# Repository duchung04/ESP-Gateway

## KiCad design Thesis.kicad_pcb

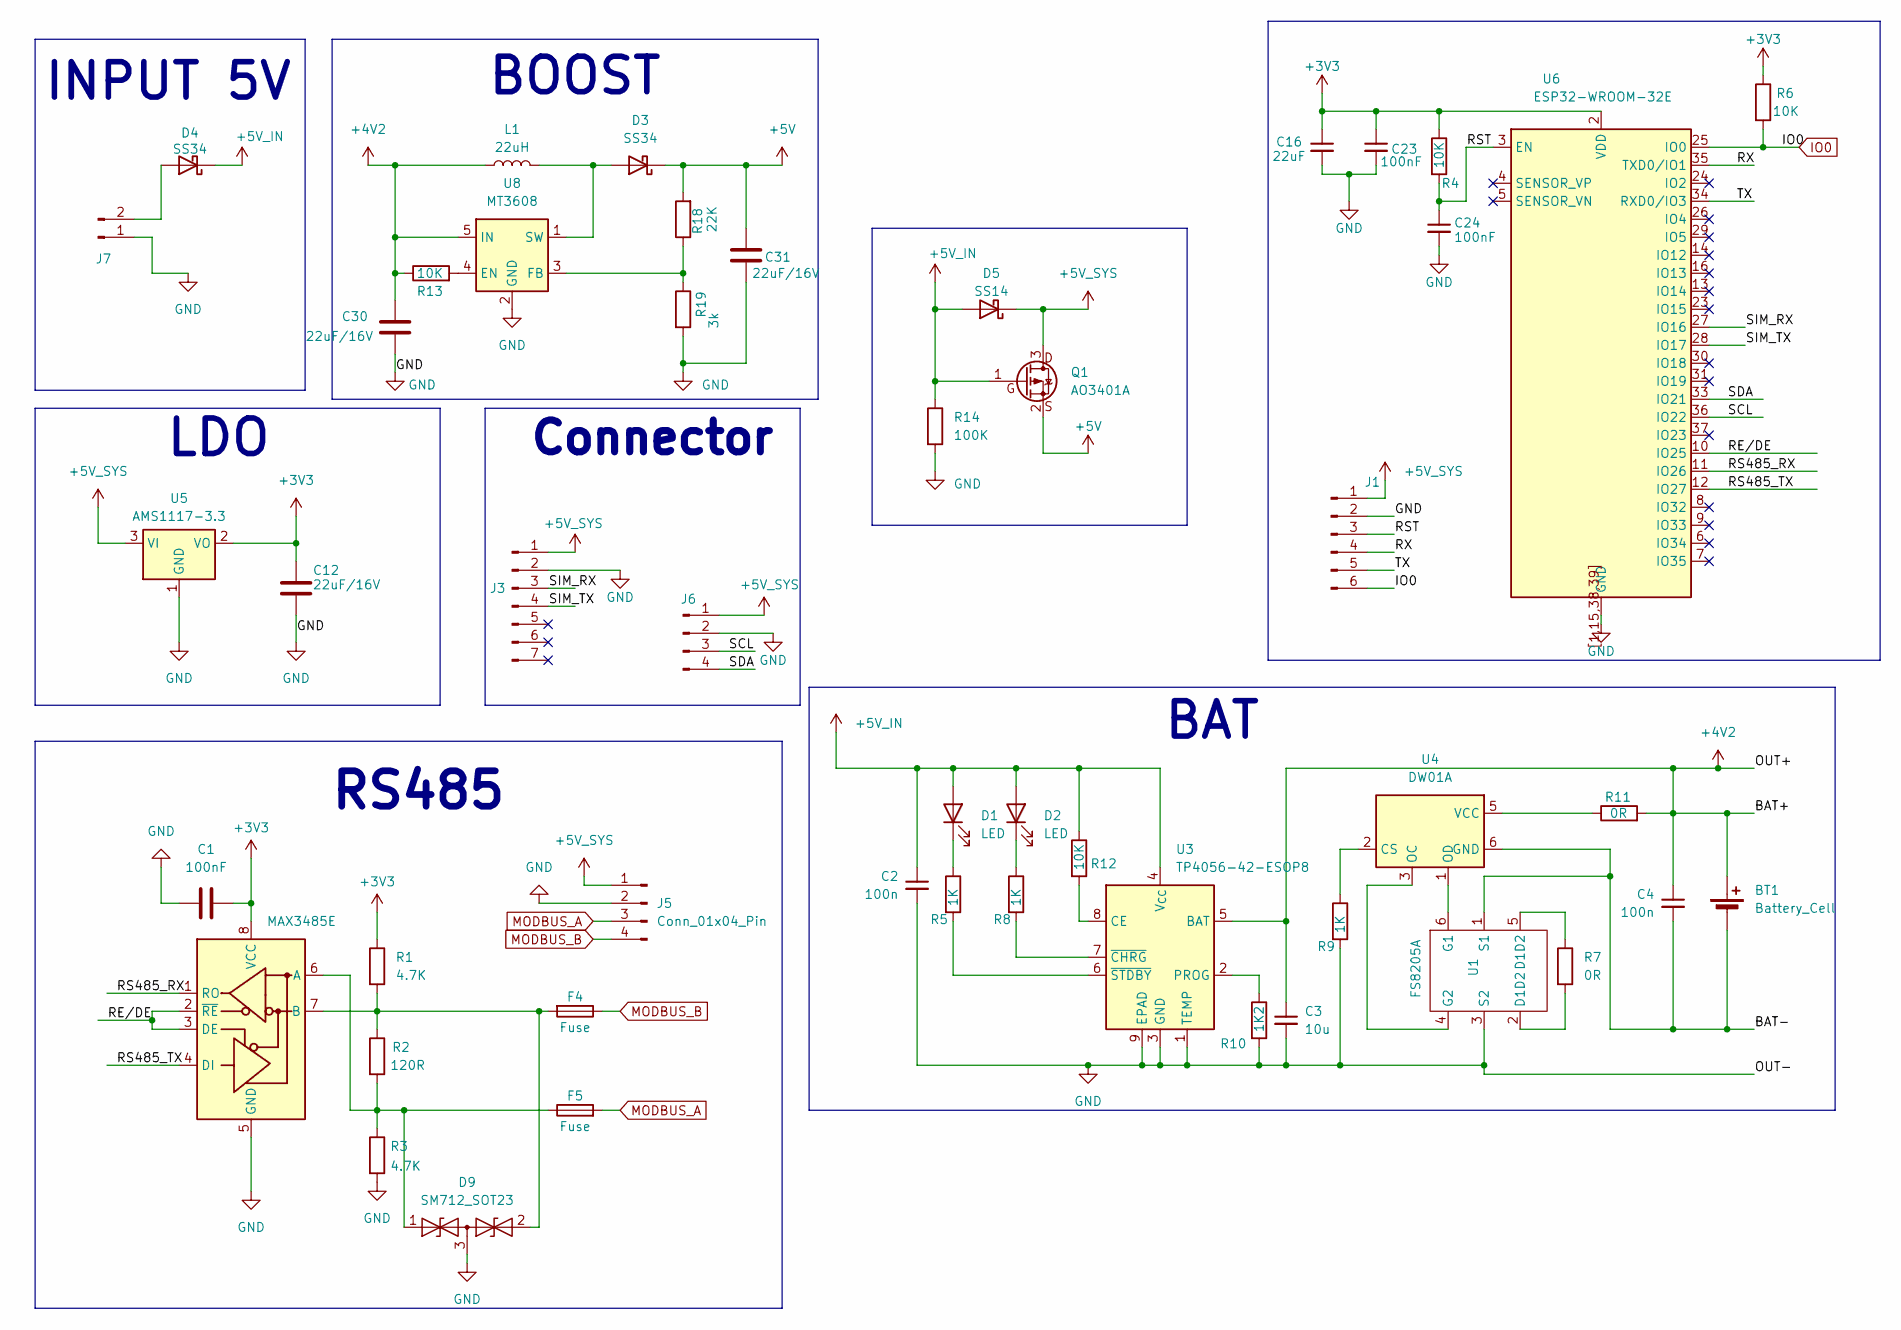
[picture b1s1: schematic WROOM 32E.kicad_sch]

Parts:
BT1: Battery_Cell; BatteryHolder_MPD_BK-18650-PC2
C1, C23, C24: 100nF; C_0603_1608Metric
C2, C4: 100n; C_0603_1608Metric
C3: 10u; C_0603_1608Metric
C12, C30, C31: 22uF/16V; C_1206_3216Metric
C16: 22uF; C_0805_2012Metric
D1, D2: LED; LED_0603_1608Metric
D3, D4: SS34; D_SMA
D5: SS14; D_SMA
D9: SM712_SOT23; SOT-23
F4, F5: Fuse; Fuse_1206_3216Metric
J1: Conn_01x06_Pin; PinHeader_1x06_P2.54mm_Vertical
J3: Conn_01x07_Pin; PinHeader_1x07_P2.54mm_Vertical
J5: Conn_01x04_Pin; PhoenixContact_MCV_1,5_4-G-3.81_1x04_P3.81mm_Vertical
J6: Conn_01x04_Pin; PinHeader_1x04_P2.54mm_Vertical
J7: Conn_01x02_Pin; PhoenixContact_MCV_1,5_2-G-3.81_1x02_P3.81mm_Vertical
L1: 22uH; L_APV_APH0630
Q1: AO3401A; SOT-23
R1, R3: 4.7K; R_0603_1608Metric
R2: 120R; R_0603_1608Metric
R4, R6, R12, R13: 10K; R_0603_1608Metric
R5, R8, R9: 1K; R_0603_1608Metric
R7: 0R; C_0603_1608Metric
R10: 1K2; R_0603_1608Metric
R11: 0R; R_0603_1608Metric
R14: 100K; C_0603_1608Metric
R18: 22K; R_0603_1608Metric
R19: 3k; R_0603_1608Metric
U1: FS8205A; SOT-23-6_Handsoldering
U3: TP4056-42-ESOP8; SOIC-8-1EP_3.9x4.9mm_P1.27mm_EP2.41x3.3mm
U4: DW01A; SOT-23-6
U5: AMS1117-3.3; SOT-223-3_TabPin2
U6: ESP32-WROOM-32E
U8: MT3608; SOT-23-6
U12: MAX3485E; SOIC-8_3.9x4.9mm_P1.27mm

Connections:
+3V3: C1.2, C12.1, C16.1, C23.1, R1.1, R4.1, R6.1, U5.2 (VO), U6.2 (VDD), U12.8 (VCC)
+4V2: BT1.1 (+), C3.1, C4.1, C30.1, L1.1, R11.2, R13.1, U3.5 (BAT), U8.5 (IN)
+5V: C31.1, D3.1 (K), Q1.2 (S), R18.2
+5V_IN: C2.1, D1.2 (A), D2.2 (A), D4.1 (K), D5.2 (A), Q1.1 (G), R12.1, R14.1, U3.4 (V_{CC})
+5V_SYS: D5.1 (K), J1.1, J3.1, J5.1, J6.1, Q1.3 (D), U5.3 (VI)
/WROOM 32E/BAT-: BT1.2 (-), C4.2, U1.1 (S1), U4.6 (GND)
/WROOM 32E/RE/DE: U6.10 (IO25), U12.2 (~RE), U12.3 (DE)
/WROOM 32E/RS485_RX: U6.11 (IO26), U12.1 (RO)
/WROOM 32E/RS485_TX: U6.12 (IO27), U12.4 (DI)
/WROOM 32E/RST: C24.1, J1.3, R4.2, U6.3 (EN)
/WROOM 32E/RX: J1.4, U6.35 (TXD0/IO1)
/WROOM 32E/SCL: J6.3, U6.36 (IO22)
/WROOM 32E/SDA: J6.4, U6.33 (IO21)
/WROOM 32E/SIM_RX: J3.3, U6.27 (IO16)
/WROOM 32E/SIM_TX: J3.4, U6.28 (IO17)
/WROOM 32E/TX: J1.5, U6.34 (RXD0/IO3)
GND: C1.1, C2.2, C3.2, C12.2, C16.2, C23.2, C24.2, C30.2, C31.2, D9.3 (common), J1.2, J3.2, J5.2, J6.2, J7.1, R3.2, R9.2, R10.2, R14.2, R19.2, U1.3 (S2), U3.1 (TEMP), U3.3 (GND), U3.9 (EPAD), U5.1 (GND), U6.1 (GND), U6.15 (GND), U6.38 (GND), U6.39 (GND), U6.[1,15,38,39] (GND), U8.2 (GND), U12.5 (GND)
IO0: J1.6, R6.2, U6.25 (IO0)
MODBUS_A: F5.2, J5.3
MODBUS_B: F4.1, J5.4
unnamed: D1.1 (K), R5.1
unnamed: D2.1 (K), R8.1
unnamed: D3.2 (A), L1.2, U8.1 (SW)
unnamed: D4.2 (A), J7.2
unnamed: D9.1 (A1), F5.1, R2.2, R3.1, U12.6 (A)
unnamed: D9.2 (A2), F4.2, R1.2, R2.1, U12.7 (B)
unnamed: R7.1, U1.5 (D1D2)
unnamed: R7.2, U1.2 (D1D2)
unnamed: U1.6 (G1), U4.1 (OD)
unnamed: U1.4 (G2), U4.3 (OC)
unnamed: R12.2, U3.8 (CE)
unnamed: R10.1, U3.2 (PROG)
unnamed: R8.2, U3.7 (~CHRG)
unnamed: R5.2, U3.6 (~STDBY)
unnamed: R9.1, U4.2 (CS)
unnamed: R11.1, U4.5 (VCC)
unnamed: R13.2, U8.4 (EN)
unnamed: R18.1, R19.1, U8.3 (FB)

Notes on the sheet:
RS485
LDO
BAT
BOOST
INPUT 5V
Connector

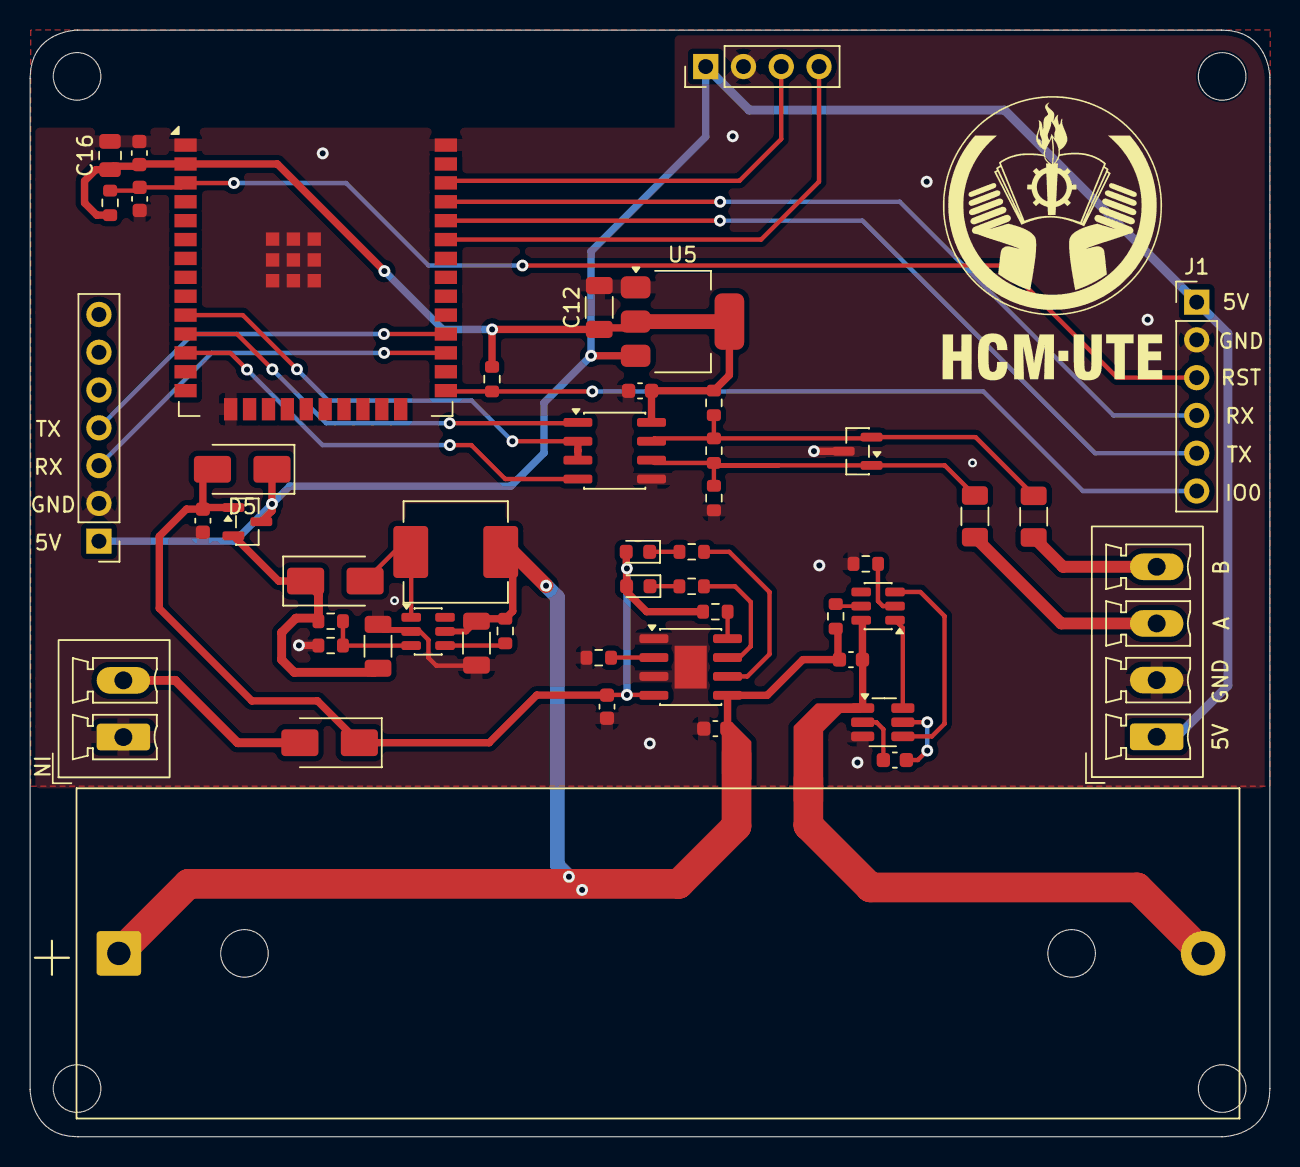
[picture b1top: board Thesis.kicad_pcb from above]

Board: 2 copper layers, 83.4 x 74.4 mm, 49 parts (0 on the bottom side), 38 nets.
